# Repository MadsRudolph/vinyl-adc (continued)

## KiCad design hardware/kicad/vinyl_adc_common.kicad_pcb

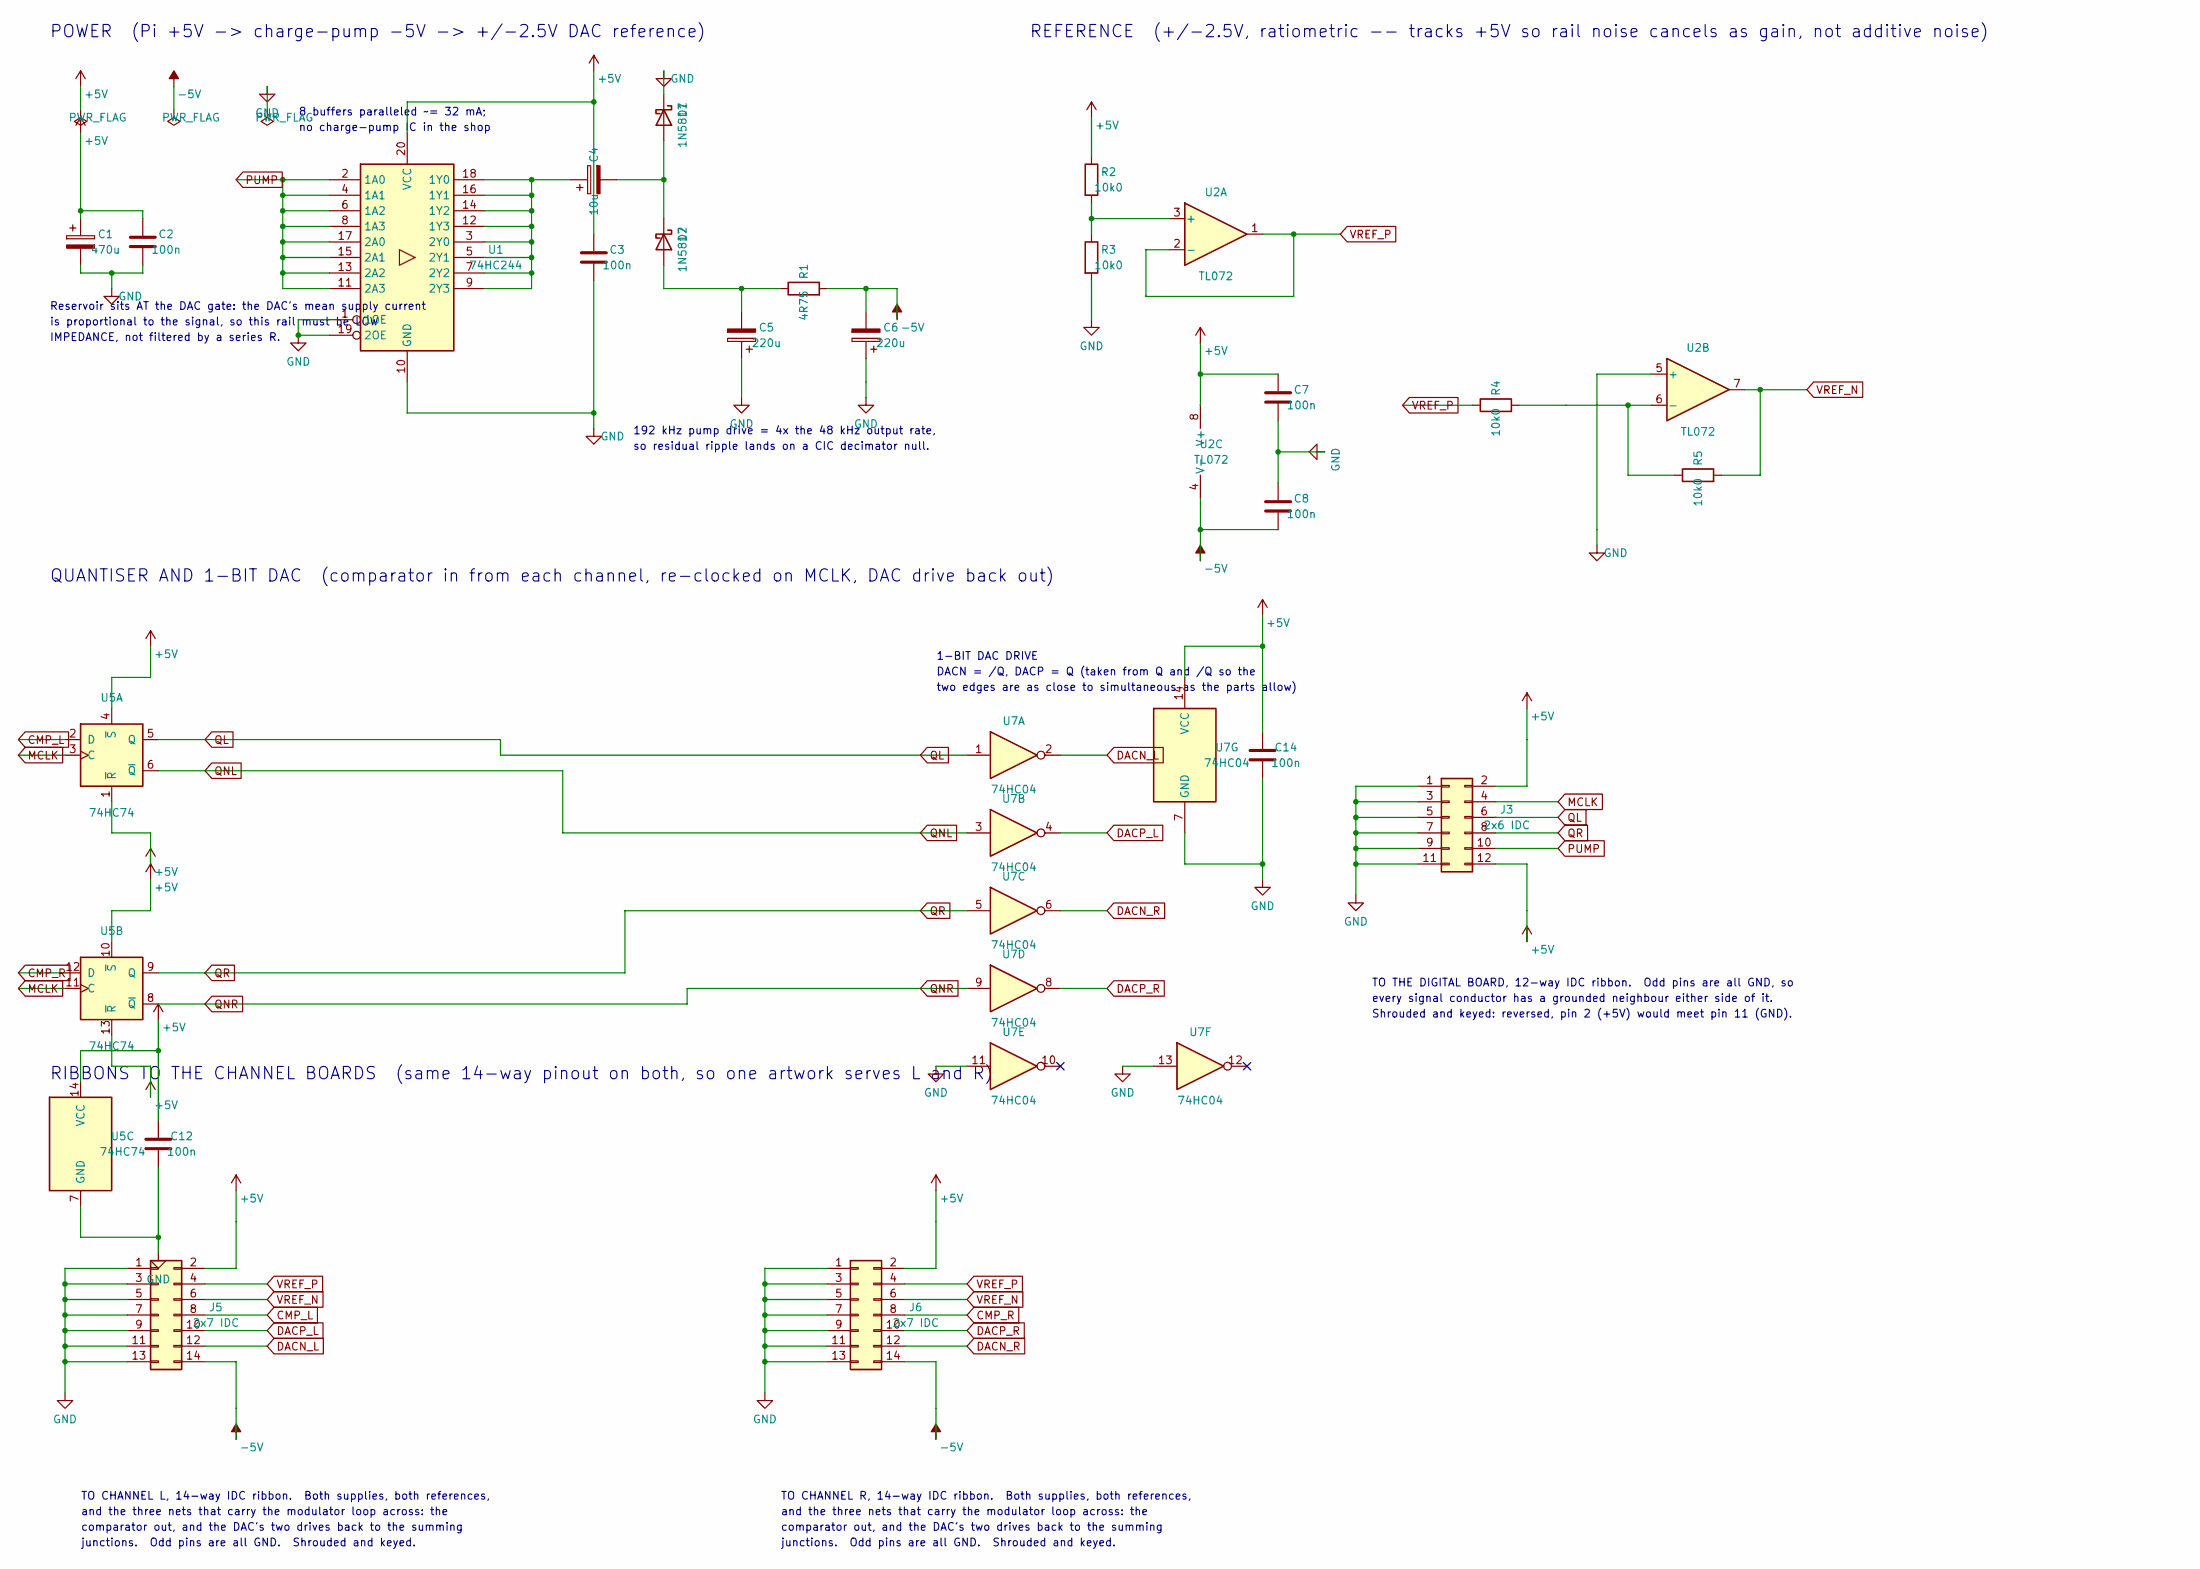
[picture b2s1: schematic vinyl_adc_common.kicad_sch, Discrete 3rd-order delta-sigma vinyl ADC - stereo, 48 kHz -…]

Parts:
C1: 470u; CP_Radial_D10.0mm_P5.00mm
C2, C3, C7, C8, C12, C14: 100n; C_Disc_D5.0mm_W2.5mm_P5.00mm
C4: 10u; CP_Radial_D8.0mm_P3.50mm
C5, C6: 220u; CP_Radial_D8.0mm_P3.50mm
D1, D2: 1N5817; D_DO-41_SOD81_P10.16mm_Horizontal
J3: 2x6 IDC; IDC-Header_2x06_P2.54mm_Vertical
J5, J6: 2x7 IDC; IDC-Header_2x07_P2.54mm_Vertical
R1: 4R75; R_Axial_DIN0207_L6.3mm_D2.5mm_P7.62mm_Horizontal
R2, R3, R4, R5: 10k0; R_Axial_DIN0207_L6.3mm_D2.5mm_P7.62mm_Horizontal
U1: 74HC244; DIP-20_W7.62mm_LongPads
U2: TL072; DIP-8_W7.62mm_LongPads
U5: 74HC74; DIP-14_W7.62mm_LongPads
U7: 74HC04; DIP-14_W7.62mm_LongPads

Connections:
CMP_L: J5.8, U5.2 (D)
CMP_R: J6.8, U5.12 (D)
DACN_L: J5.12, U7.2
DACN_R: J6.12, U7.6
DACP_L: J5.10, U7.4
DACP_R: J6.10, U7.8
MCLK: J3.4, U5.3 (C), U5.11 (C)
unnamed: C4.2, D1.2 (A), D2.1 (K)
unnamed: C5.2, D2.2 (A), R1.1
unnamed: C4.1, U1.3 (2Y0), U1.5 (2Y1), U1.7 (2Y2), U1.9 (2Y3), U1.12 (1Y3), U1.14 (1Y2), U1.16 (1Y1), U1.18 (1Y0)
unnamed: R2.2, R3.1, U2.3 (+)
unnamed: R4.2, R5.1, U2.6 (-)
PUMP: J3.10, U1.2 (1A0), U1.4 (1A1), U1.6 (1A2), U1.8 (1A3), U1.11 (2A3), U1.13 (2A2), U1.15 (2A1), U1.17 (2A0)
QL: J3.6, U5.5 (Q), U7.1
QNL: U5.6 (~Q), U7.3
QNR: U5.8 (~Q), U7.9
QR: J3.8, U5.9 (Q), U7.5
VREF_N: J5.6, J6.6, R5.2, U2.7
VREF_P: J5.4, J6.4, R4.1, U2.1, U2.2 (-)

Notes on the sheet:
POWER (Pi +5V -> charge-pump -5V -> +/-2.5V DAC reference)
Reservoir sits AT the DAC gate: the DAC's mean supply current
is proportional to the signal, so this rail must be LOW
IMPEDANCE, not filtered by a series R.
8 buffers paralleled ~= 32 mA;
no charge-pump IC in the shop
192 kHz pump drive = 4x the 48 kHz output rate,
so residual ripple lands on a CIC decimator null.
REFERENCE (+/-2.5V, ratiometric -- tracks +5V so rail noise cancels as gain, not additive noise)
QUANTISER AND 1-BIT DAC (comparator in from each channel, re-clocked on MCLK, DAC drive back out)
1-BIT DAC DRIVE
DACN = /Q, DACP = Q (taken from Q and /Q so the
two edges are as close to simultaneous as the parts allow)
TO THE DIGITAL BOARD, 12-way IDC ribbon. Odd pins are all GND, so
every signal conductor has a grounded neighbour either side of it.
Shrouded and keyed: reversed, pin 2 (+5V) would meet pin 11 (GND).
RIBBONS TO THE CHANNEL BOARDS (same 14-way pinout on both, so one artwork serves L and R)
TO CHANNEL L, 14-way IDC ribbon. Both supplies, both references,
and the three nets that carry the modulator loop across: the
comparator out, and the DAC's two drives back to the summing
junctions. Odd pins are all GND. Shrouded and keyed.
TO CHANNEL R, 14-way IDC ribbon. Both supplies, both references,

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
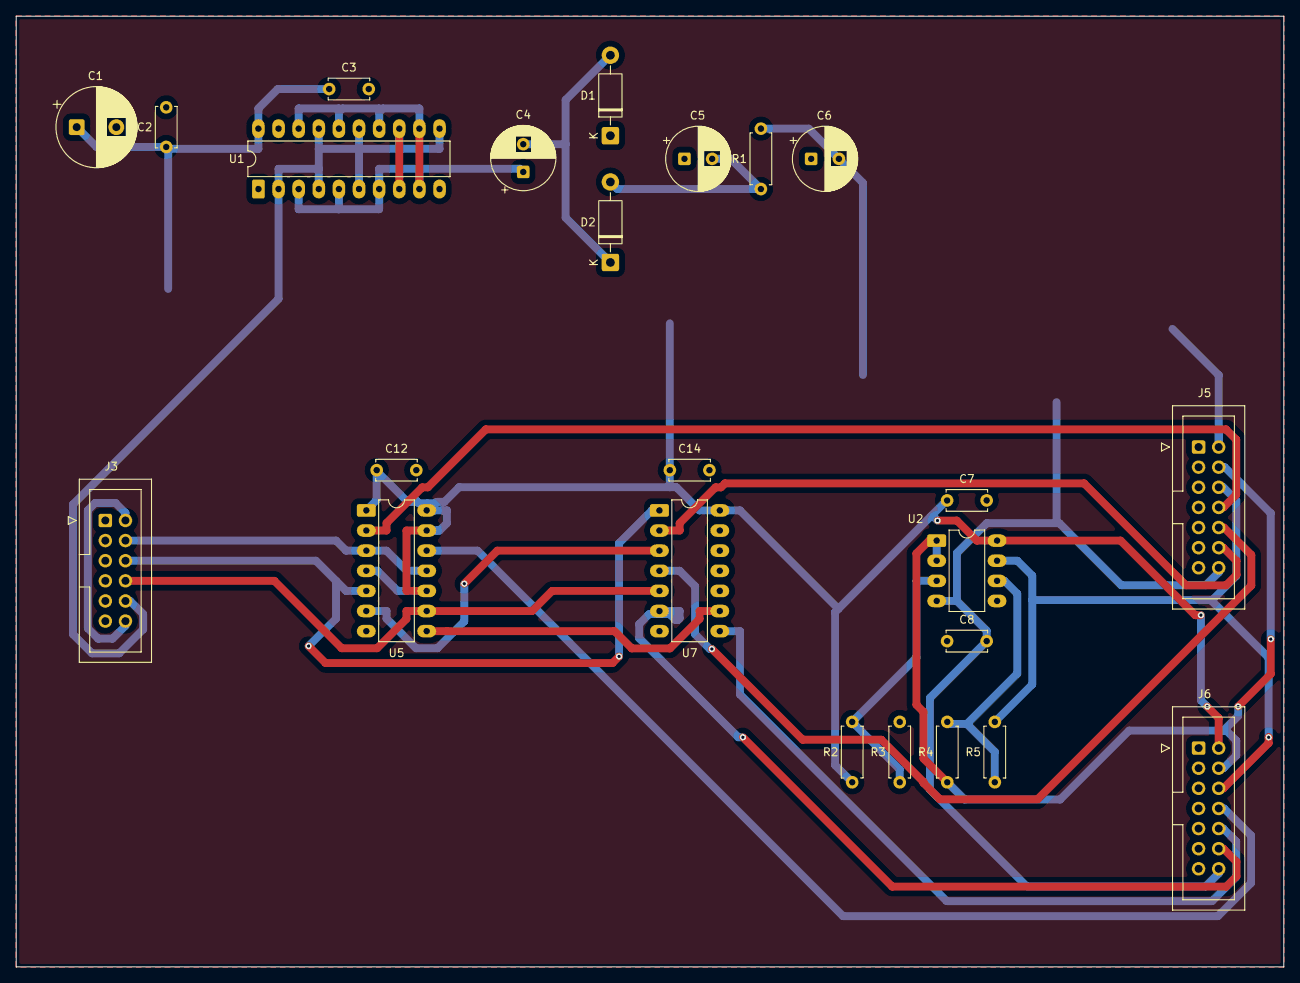
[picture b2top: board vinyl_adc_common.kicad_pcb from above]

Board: 2 copper layers, 160.0 x 120.0 mm, 24 parts (0 on the bottom side), 22 nets.
